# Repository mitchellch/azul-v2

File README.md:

# Azul Sprinkler System

## Main Purpose
The Azul Sprinkler System is a comprehensive, open-source irrigation control ecosystem designed for flexibility, resilience, and remote management. It is architected to support both standard wired irrigation zones and wireless, battery-operated "Zone Extenders" for areas without existing infrastructure. The entire system—from mobile app to firmware—is managed within this monorepo.

## Project Structure
This repository is a monorepo containing all components of the Azul system.

- **`mobile/`**: A cross-platform (iOS/Android) mobile application built with React Native and Expo. This is the primary user interface for controlling and monitoring the system.
- **`server/`**: The backend API and services. This component will handle business logic, data persistence, and communication between the apps and the hardware controllers. *(Not yet implemented)*
- **`firmware/`**: ESP32-based firmware for the physical sprinkler controllers. This includes code for the mains-powered Main Controller and the battery-powered Zone Extenders. *(Not yet implemented)*
- **`shared/`**: A directory for shared code, such as TypeScript types, constants, or validation schemas, that can be used across the mobile, server, and potentially firmware components.
- **`docs/`**: Contains all project documentation, including architecture diagrams, specifications, and bills of materials.

## Key Documentation
- **[Overall Architecture](docs/design/architecture.md):** A high-level overview of the entire system, its components, and how they interact.
- **[Zone Extender Specification](docs/design/zone-extender-spec.md):** Detailed technical specifications for the battery-powered, LoRa-based zone controller.
- **[Main Controller Bill of Materials](docs/hardware/main-controller-bom.md):** A complete list of electronic components for the main, wall-powered controller.

## Prerequisites

| Tool | Version | Notes |
|---|---|---|
| Node.js | 25.x | `node -v` to check |
| npm | 11.x | Ships with Node |
| Docker Desktop | 29.x+ | Runs PostgreSQL and Mosquitto |
| Android Studio | Panda 4+ | SDK, emulator, and `adb` |
| JDK 17 (Azul Zulu) | 17.x | At `/Library/Java/JavaVirtualMachines/zulu-17.jdk` |
| PlatformIO | Latest | VS Code extension or CLI — for firmware only |

Required shell config (`~/.zshrc`):

```bash
export JAVA_HOME=/Library/Java/JavaVirtualMachines/zulu-17.jdk/Contents/Home
export PATH=$JAVA_HOME/bin:$PATH
export ANDROID_HOME=$HOME/Library/Android/sdk
export PATH=$PATH:$ANDROID_HOME/platform-tools
```

> **macOS managed machine note:** A Salesforce Java stub at `/usr/local/bin/java` intercepts the `java` command. The `$JAVA_HOME/bin` prepend to `PATH` overrides it. If `java -version` shows a Salesforce warning instead of the JDK version, run `source ~/.zshrc`.

## Development Setup

The dev environment runs across **five terminal tabs** plus an Android emulator. Tabs are numbered by position, not startup order. Start services in this order: **Tab 5 (Docker) → Tab 4 (Server) → Tabs 2 & 3 (Mobile & Web, either order)**.

| Tab | Name | Description |
|-----|------|-------------|
| 1 | **Claude Code** | AI development agent (Anthropic CLI). Primary interaction point for editing code, running commands, and managing git. |
| 2 | **Mobile (Expo/React Native)** | Android app via `npx expo run:android`. BLE + cloud zone control, schedules, Auth0 native auth. |
| 3 | **Web (Next.js Dashboard)** | Next.js 14 browser dashboard on port 3001. Auth0 server-side sessions, REST proxy to backend, SSE zone updates, Tailwind CSS. |
| 4 | **Server (Express.js API)** | Node.js/TypeScript backend on port 3000. REST API, Auth0 JWT auth, Prisma ORM, MQTT client, SSE streams. |
| 5 | **Docker (Postgres + Mosquitto)** | Infrastructure services via Docker Compose. PostgreSQL 16 database and Eclipse Mosquitto 2 MQTT broker. Must start first. |
| — | **Firmware (VS Code + PlatformIO)** | Not a terminal tab. ESP32-S3 firmware built/flashed/monitored from VS Code with the PlatformIO extension. |

### 0. Connect an Android device

`npx expo run:android` needs a target device — either a physical phone or the emulator.

- **Physical phone (current setup):** Connect via USB with Developer Options and USB Debugging enabled. Run `adb devices` to confirm it appears.
- **Emulator (optional):** Open Android Studio → Device Manager → ▶ play on Pixel 9 (API 35). Wait for the home screen before proceeding.

### Tab 1 — Claude Code

```bash
cd ~/personal/dev/azul
claude
```

| | Details |
|---|---|
| **Tool** | Claude Code (Anthropic CLI) |
| **What it does** | AI-assisted development agent running in the terminal. Has full access to the repo for editing code, running commands, searching files, and managing git. This is the primary tab you interact with during development. |

### Tab 2 — Mobile app

```bash
cd mobile
npx expo run:android
```

| | Details |
|---|---|
| **Framework** | React Native 0.81 + Expo SDK 54 (TypeScript) |
| **Build tool** | Expo CLI — compiles native Android binary with linked native modules, then starts Metro bundler |
| **What it does** | Primary user interface. Auth via `react-native-auth0`, BLE communication via `react-native-ble-plx`, cloud communication via REST polling to the backend API. Manages zone control (start/stop/queue), schedules, and controller settings. |
| **Key env vars** | `EXPO_PUBLIC_API_URL`, `EXPO_PUBLIC_AUTH0_DOMAIN`, `EXPO_PUBLIC_AUTH0_CLIENT_ID` (in `mobile/.env` and `mobile/.env.local`) |

> **Important:** This project uses native modules (BLE, Auth0) that require a development build. **Do NOT use `npx expo start`** — that launches Expo Go, which cannot load native modules. Always use `npx expo run:android`.

> **Env var changes:** `EXPO_PUBLIC_*` vars are baked in at Metro startup. After editing `.env` or `.env.local`, restart Metro with `npx expo start --reset-cache`, then press `a` to relaunch on Android.

First build takes 2–3 minutes (compiles native code). Subsequent runs are faster (~30s). The app installs and launches on the emulator automatically.

### Tab 3 — Web dashboard

```bash
cd web
npm run dev
```

| | Details |
|---|---|
| **Framework** | Next.js 14 (TypeScript, App Router) |
| **Port** | `localhost:3001` |
| **What it does** | Browser-based dashboard for controlling irrigation. Auth via `@auth0/nextjs-auth0` (server-side sessions). Proxies API requests to the backend at `localhost:3000`. Receives real-time zone updates via SSE (Server-Sent Events) through a fetch-based stream. Styled with Tailwind CSS. |
| **Key env vars** | `AUTH0_SECRET`, `AUTH0_BASE_URL`, `AUTH0_ISSUER_BASE_URL`, `AUTH0_CLIENT_ID`, `AUTH0_CLIENT_SECRET`, `AUTH0_AUDIENCE`, `NEXT_PUBLIC_API_URL` (in `web/.env.local`) |

Open `http://localhost:3001` in a browser. You'll be redirected to Auth0 for login (Google OAuth).

### Tab 4 — Backend API server

```bash
cd server
npm run dev
```

| | Details |
|---|---|
| **Framework** | Express.js (Node.js / TypeScript) |
| **Runner** | `tsx watch` — auto-reloads on file changes |
| **Port** | `localhost:3000` |
| **What it does** | REST API for devices, zones, schedules, and users. Authenticates requests via Auth0 JWTs. Connects to PostgreSQL via Prisma ORM and to Mosquitto via MQTT.js. Maintains an in-memory zone state cache from MQTT status messages. Serves SSE streams to the web app. Runs an offline-sweep job to detect disconnected controllers. |
| **Key env vars** | `DATABASE_URL`, `MQTT_URL`, `AUTH0_DOMAIN`, `AUTH0_AUDIENCE` (in `server/.env`) |

You should see `Server listening on port 3000` and `[MQTT] Connected to mqtt://localhost:1883`.

### Tab 5 — Docker infrastructure

```bash
cd server
docker compose up
```

| What it runs | Details |
|---|---|
| **PostgreSQL 16** (Alpine) | Relational database. Stores users, devices, zones, schedules, audit logs. Accessible at `localhost:5432`, credentials `azul/azul/azul` (user/password/database). Data persists in a Docker volume (`postgres_data`). |
| **Eclipse Mosquitto 2** | MQTT message broker. Relays commands and status between the backend server and ESP32 controllers. Listens on `localhost:1883` (MQTT) and `localhost:9001` (WebSocket). Anonymous access enabled for local dev. |

Leave this tab running. You should see `database system is ready to accept connections` and `mosquitto version 2.x.x running`.

### Firmware (VS Code + PlatformIO)

Firmware development uses **VS Code with the PlatformIO extension** — not a terminal tab. Open the `firmware/main-controller` folder in VS Code as a PlatformIO project.

| Action | How |
|---|---|
| **Build** | PlatformIO sidebar → Build, or `pio run -e esp32-s3` |
| **Flash** | Connect ESP32 via USB → PlatformIO sidebar → Upload, or `pio run --target upload -e esp32-s3` |
| **Serial monitor** | PlatformIO sidebar → Monitor, or `pio device monitor --baud 115200` |
| **Build + Flash + Monitor** | PlatformIO sidebar → Upload and Monitor |

| | Details |
|---|---|
| **Platform** | ESP32-S3 (N16R8), Arduino framework |
| **Build system** | PlatformIO |
| **What it does** | Runs on the physical irrigation controller. Manages zone GPIOs (solenoid drivers), WiFi connectivity, MQTT communication with the backend, BLE GATT server for mobile app pairing, NTP time sync, schedule execution, and a serial CLI for debugging. |
| **Integration tests** | `python3 -m pytest tests/integration/ --host=<controller-ip> -q` (requires controller on same network) |

### Service dependency graph

```
Docker (Postgres + Mosquitto)
  └── Backend API server (connects to both)
        ├── Mobile app (REST polling to backend)
        ├── Web app (REST proxy + SSE from backend)
        └── ESP32 firmware (MQTT via Mosquitto)
```

### First-time setup

If this is a fresh clone or the Docker volume was wiped:

```bash
cd server
npm install
npx prisma db push       # creates tables in PostgreSQL
npx prisma generate       # generates the Prisma client

cd ../mobile
npm install

cd ../web
npm install
```

### Stopping everything

1. **Ctrl+C** in each terminal tab (mobile, server, web, Docker)
2. Close the Android emulator from Android Studio Device Manager
3. Docker volumes persist — your database data survives restarts

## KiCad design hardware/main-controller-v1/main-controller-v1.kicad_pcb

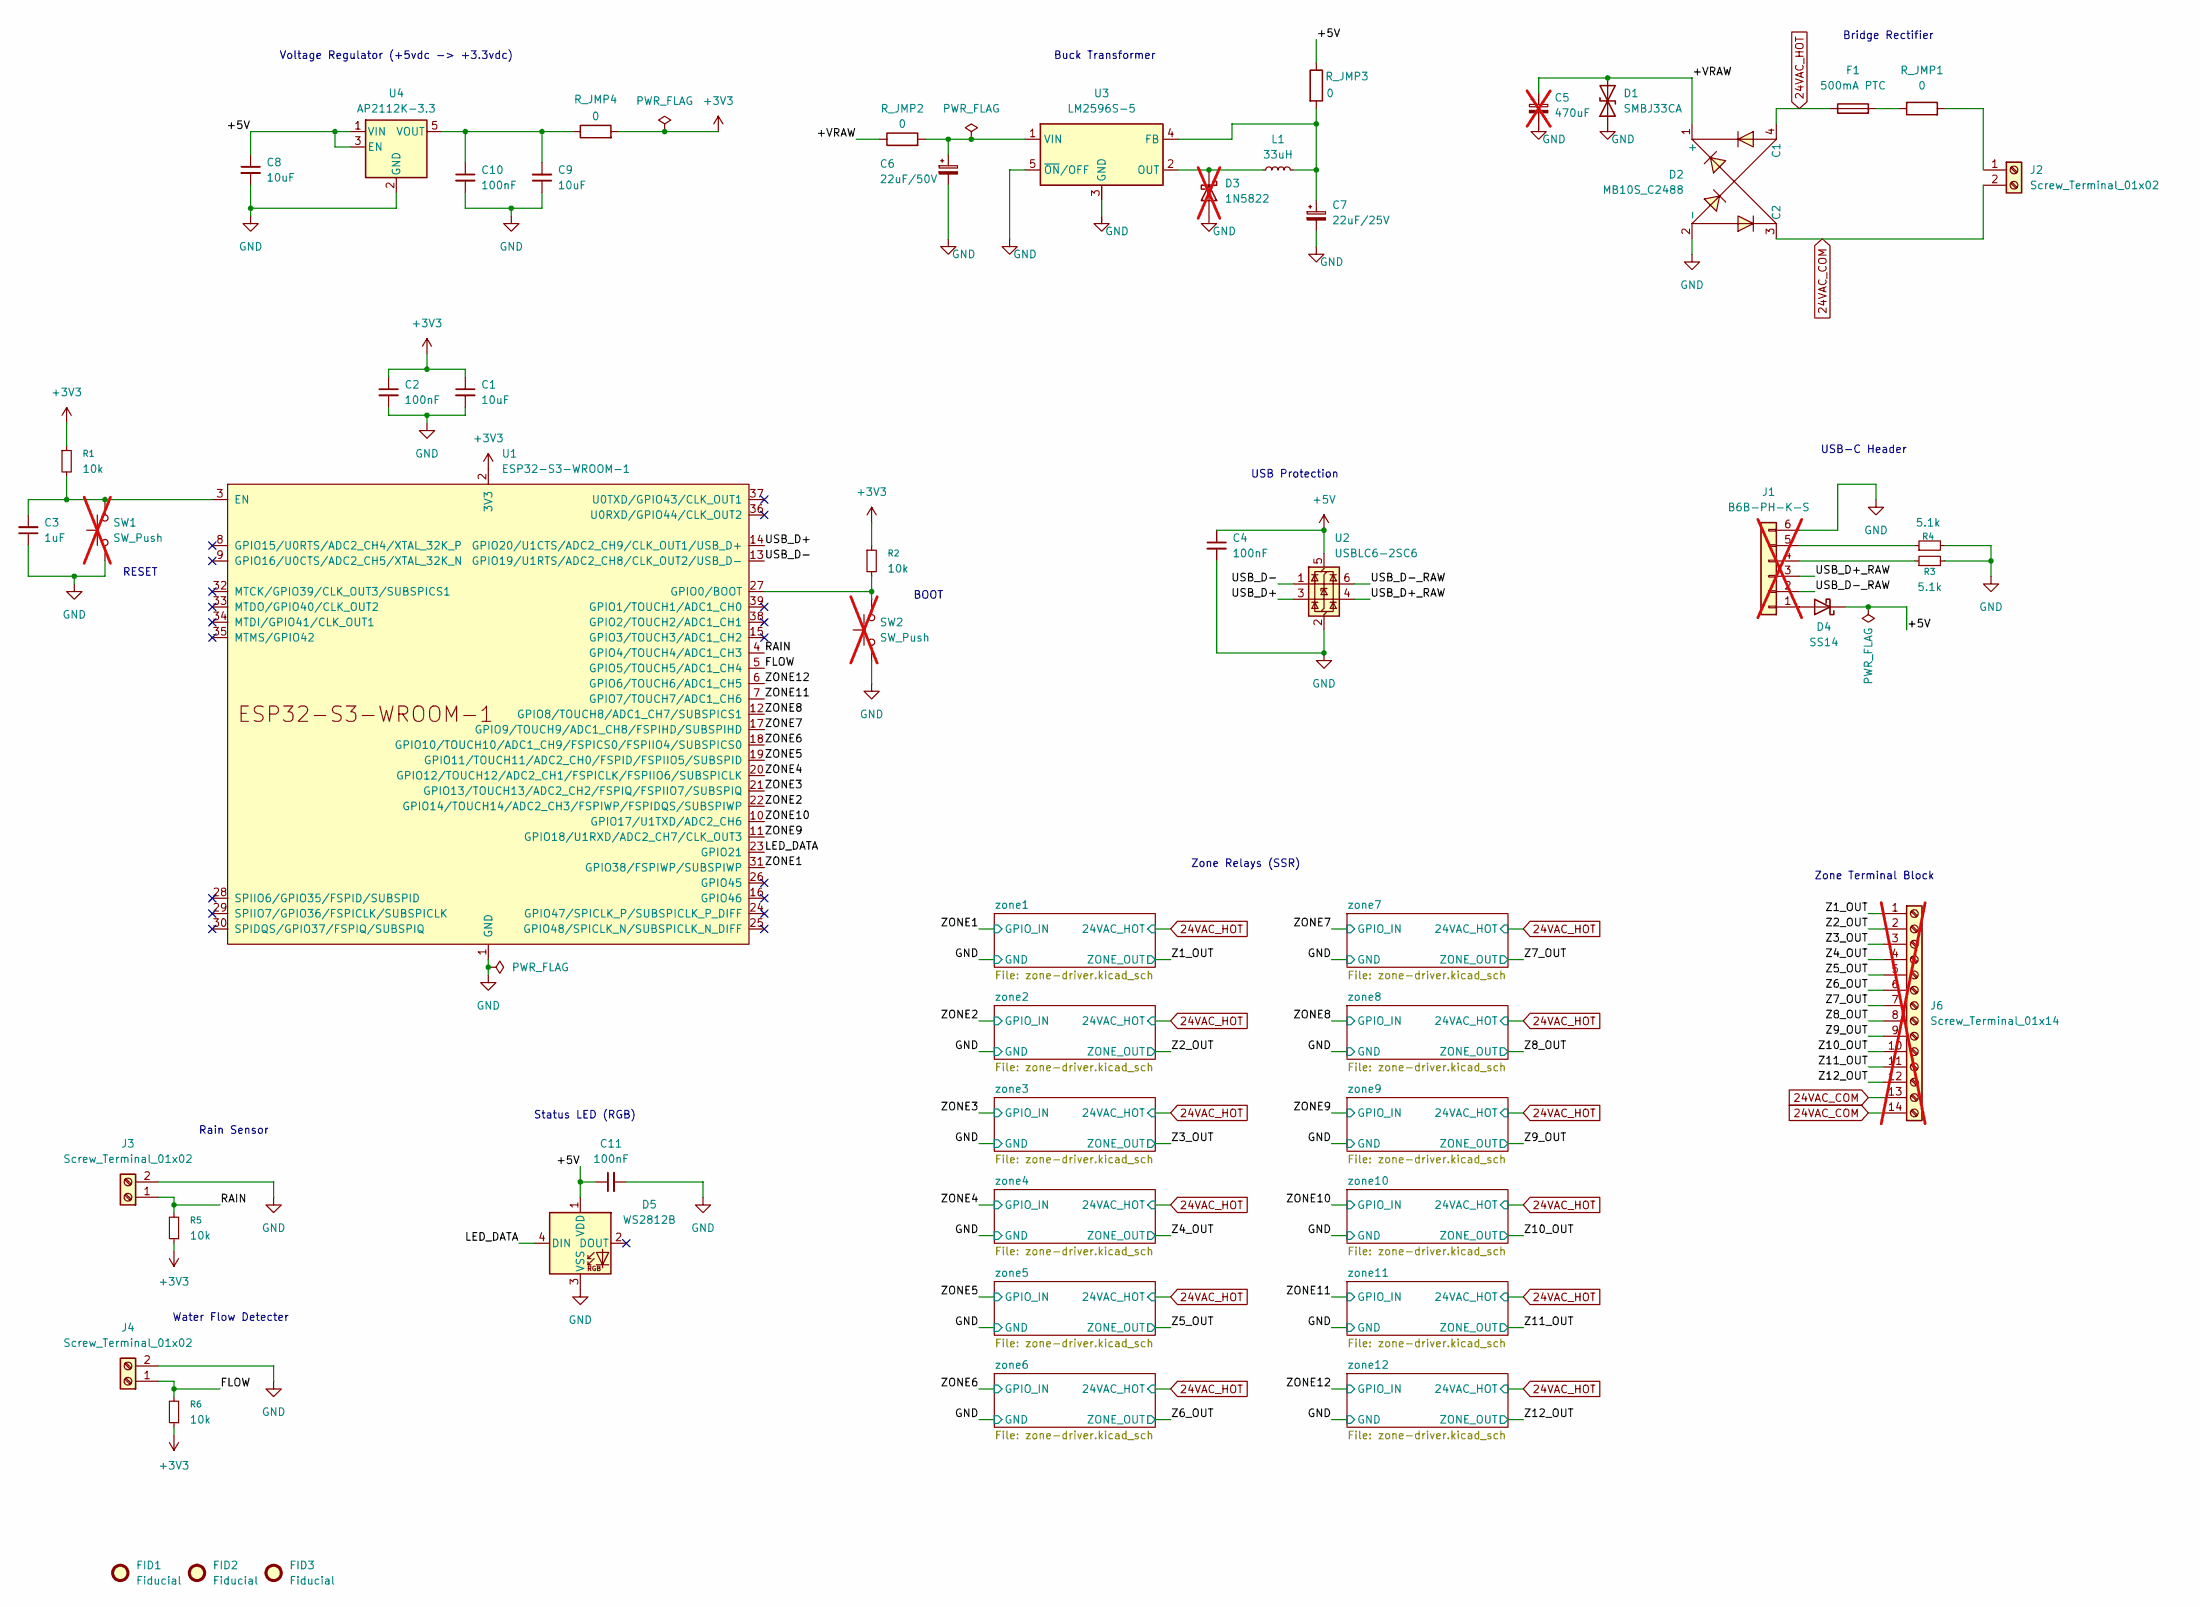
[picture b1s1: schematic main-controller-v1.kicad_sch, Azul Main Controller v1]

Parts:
C1, C8, C9: 10uF; C_0805_2012Metric; LCSC C15850
C2, C4, C10, C11: 100nF; C_0603_1608Metric; LCSC C14663
C3: 1uF; C_0603_1608Metric; LCSC C15849
C5: 470uF; CP_Radial_D10.0mm_P5.00mm; not fitted
C6: 22uF/50V; CP_Elec_6.3x5.4; LCSC C2836438
C7: 22uF/25V; CP_Elec_5x5.8; LCSC C178541
D1: SMBJ33CA; D_SMB; LCSC C78420
D2: MB10S_C2488; MBS_L4.7-W3.8-P2.40-LS7.0-TL; MPN MB10S-50MIL; LCSC C2488
D3: 1N5822; D_DO-201AD_P15.24mm_Horizontal; not fitted
D4: SS14; D_SMA; LCSC C2480
D5: WS2812B; LED_WS2812B_PLCC4_5.0x5.0mm_P3.2mm; LCSC C2761795
F1: 500mA PTC; Fuse_1812_4532Metric; LCSC C17313
FID1, FID2, FID3: Fiducial; Fiducial_1mm_Mask2mm
J1: B6B-PH-K-S; JST_PH_B6B-PH-K_1x06_P2.00mm_Vertical; LCSC C131357; not fitted
J2, J3, J4: Screw_Terminal_01x02; TerminalBlock_MaiXu_MX126-5.0-02P_1x02_P5.00mm; LCSC C5188434
J6: Screw_Terminal_01x14; TerminalBlock_MaiXu_MX126-5.0-14P_1x14_P5.00mm; not fitted
L1: 33uH; L_Bourns_SRR1260; LCSC C840528
R1, R2, R5, R6: 10k; R_0603_1608Metric; LCSC C25804
R3, R4: 5.1k; R_0603_1608Metric; LCSC C23186
R_JMP1, R_JMP2, R_JMP3, R_JMP4: 0; R_1206_3216Metric; LCSC C17168
SW1, SW2: SW_Push; SW_PUSH_6mm; not fitted
U1: ESP32-S3-WROOM-1; LCSC C2913204
U2: USBLC6-2SC6; SOT-23-6; LCSC C7519
U3: LM2596S-5; TO-263-5_TabPin3; LCSC C5276750
U4: AP2112K-3.3; SOT-23-5; LCSC C51118

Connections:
24VAC_COM: D2.3 (C2), J2.2, J6.13, J6.14
24VAC_HOT: D2.4 (C1), F1.1; also elsewhere on the board
+3V3: C1.1, C2.1, R1.1, R2.1, R5.1, R6.1, R_JMP4.2, U1.2 (3V3)
+5V: C4.1, C8.1, C11.1, D4.1 (K), D5.1 (VDD), R_JMP3.1, U2.5 (VBUS), U4.1 (VIN), U4.3 (EN)
/+VRAW: C5.1, D1.2 (A2), D2.1 (+), R_JMP2.1
/FLOW: J4.1, R6.2, U1.5 (GPIO5/TOUCH5/ADC1_CH4)
/LED_DATA: D5.4 (DIN), U1.23 (GPIO21)
/RAIN: J3.1, R5.2, U1.4 (GPIO4/TOUCH4/ADC1_CH3)
/USB_D+: U1.14 (GPIO20/U1CTS/ADC2_CH9/CLK_OUT1/USB_D+), U2.3 (I/O2)
/USB_D+_RAW: J1.3, U2.4 (I/O2)
/USB_D-: U1.13 (GPIO19/U1RTS/ADC2_CH8/CLK_OUT2/USB_D-), U2.1 (I/O1)
/USB_D-_RAW: J1.2, U2.6 (I/O1)
/Z1_OUT: J6.1; also elsewhere on the board
/Z2_OUT: J6.2; also elsewhere on the board
/Z3_OUT: J6.3; also elsewhere on the board
/Z4_OUT: J6.4; also elsewhere on the board
/Z5_OUT: J6.5; also elsewhere on the board
/Z6_OUT: J6.6; also elsewhere on the board
/Z7_OUT: J6.7; also elsewhere on the board
/Z8_OUT: J6.8; also elsewhere on the board
/Z9_OUT: J6.9; also elsewhere on the board
/Z10_OUT: J6.10; also elsewhere on the board
/Z11_OUT: J6.11; also elsewhere on the board
/Z12_OUT: J6.12; also elsewhere on the board
/ZONE1: U1.31 (GPIO38/FSPIWP/SUBSPIWP); also elsewhere on the board
/ZONE2: U1.22 (GPIO14/TOUCH14/ADC2_CH3/FSPIWP/FSPIDQS/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); also elsewhere on the board
/ZONE3: U1.21 (GPIO13/TOUCH13/ADC2_CH2/FSPIQ/FSPIIO7/S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); also elsewhere on the board
/ZONE4: U1.20 (GPIO12/TOUCH12/ADC2_CH1/FSPICLK/FSPIIO6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); also elsewhere on the board
/ZONE5: U1.19 (GPIO11/TOUCH11/ADC2_CH0/FSPID/FSPIIO5/S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); also elsewhere on the board
/ZONE6: U1.18 (GPIO10/TOUCH10/ADC1_CH9/FSPICS0/FSPIIO4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); also elsewhere on the board
/ZONE7: U1.17 (GPIO9/TOUCH9/ADC1_CH8/FSPIHD/SUBSPIHD); also elsewhere on the board
/ZONE8: U1.12 (GPIO8/TOUCH8/ADC1_CH7/SUBSPICS1); also elsewhere on the board
/ZONE9: U1.11 (GPIO18/U1RXD/ADC2_CH7/CLK_OUT3); also elsewhere on the board
/ZONE10: U1.10 (GPIO17/U1TXD/ADC2_CH6); also elsewhere on the board
/ZONE11: U1.7 (GPIO7/TOUCH7/ADC1_CH6); also elsewhere on the board
/ZONE12: U1.6 (GPIO6/TOUCH6/ADC1_CH5); also elsewhere on the board
GND: C1.2, C2.2, C3.1, C4.2, C5.2, C6.2, C7.2, C8.2, C9.1, C10.2, C11.2, D1.1 (A1), D2.2 (-), D3.2 (A), D5.3 (VSS), J1.6, J3.2, J4.2, R3.2, R4.2, SW1.1, SW2.1, U1.1 (GND), U1.40 (GND), U1.41 (GND), U2.2 (GND), U3.3 (GND), U3.5 (~ON/OFF), U4.2 (GND); also elsewhere on the board
unnamed: D3.1 (K), L1.1, U3.2 (OUT)
unnamed: D4.2 (A), J1.1
unnamed: F1.2, R_JMP1.1
unnamed: J1.4, R3.1
unnamed: J1.5, R4.1
unnamed: J2.1, R_JMP1.2
unnamed: C3.2, R1.2, SW1.2, U1.3 (EN)
unnamed: R2.2, SW2.2, U1.27 (GPIO0/BOOT)
unnamed: C7.1, L1.2, R_JMP3.2, U3.4 (FB)
unnamed: C6.1, R_JMP2.2, U3.1 (VIN)
unnamed: C9.2, C10.1, R_JMP4.1, U4.5 (VOUT)

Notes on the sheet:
Zone Terminal Block
BOOT
Buck Transformer
Voltage Regulator (+5vdc -> +3.3vdc)
USB Protection
USB-C Header
Zone Relays (SSR)
Status LED (RGB)
Rain Sensor
RESET
Water Flow Detecter
Bridge Rectifier

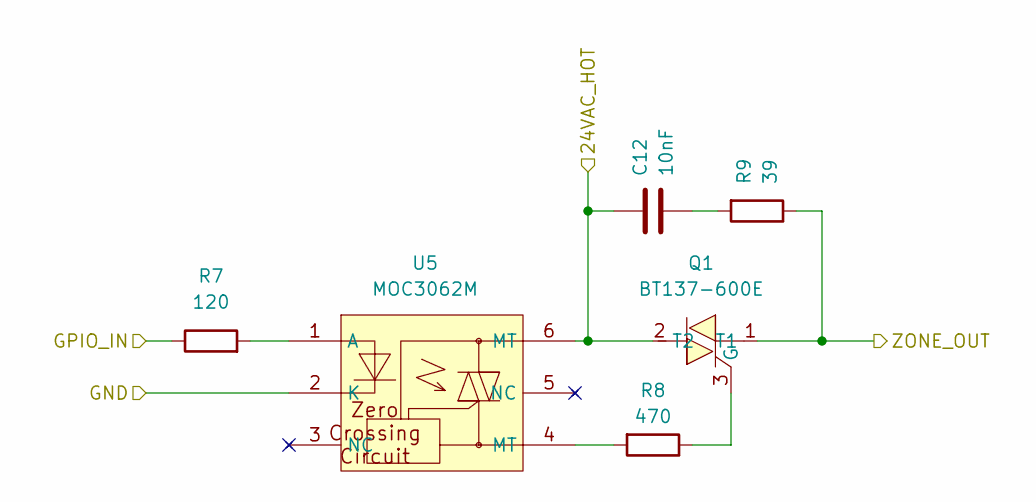
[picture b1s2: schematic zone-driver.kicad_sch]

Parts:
C12: 10nF; CAP-TH_L13.0-W5.0-P10.00-D1.0; LCSC C105755
Q1: BT137-600E; TO-220-3_L10.0-W4.5-P2.54-L; MPN BT137-600E; LCSC C967624
R7: 120; R_0805_2012Metric; LCSC C17437
R8: 470; R_0805_2012Metric; LCSC C17710
R9: 39; R_2010_5025Metric; LCSC C2692665
U5: MOC3062M; DIP-6_L8.5-W6.4-P2.54-LS7.6-BL; MPN MOC3062M; LCSC C8919

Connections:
24VAC_HOT: C12.1, Q1.2 (T2), U5.6 (MT); also elsewhere on the board
/Z1_OUT: Q1.1 (T1), R9.1; also elsewhere on the board
/ZONE1: R7.1; also elsewhere on the board
GND: U5.2 (K); also elsewhere on the board
unnamed: C12.2, R9.2
unnamed: Q1.3 (G), R8.1
unnamed: R8.2, U5.4 (MT)
unnamed: R7.2, U5.1 (A)

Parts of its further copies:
C13, C14, C15, C16, C17, C18, C19, C20, C21, C22, C23: 10nF; CAP-TH_L13.0-W5.0-P10.00-D1.0; LCSC C105755
Q2, Q3, Q4, Q5, Q6, Q7, Q8, Q9, Q10, Q11, Q12: BT137-600E; TO-220-3_L10.0-W4.5-P2.54-L; MPN BT137-600E; LCSC C967624
R10, R13, R16, R19, R22, R25, R28, R31, R34, R37, R40: 120; R_0805_2012Metric; LCSC C17437
R11, R14, R17, R20, R23, R26, R29, R32, R35, R38, R41: 470; R_0805_2012Metric; LCSC C17710
R12, R15, R18, R21, R24, R27, R30, R33, R36, R39, R42: 39; R_2010_5025Metric; LCSC C2692665
U6, U7, U8, U9, U10, U11, U12, U13, U14, U15, U16: MOC3062M; DIP-6_L8.5-W6.4-P2.54-LS7.6-BL; MPN MOC3062M; LCSC C8919

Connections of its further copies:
24VAC_HOT: C13.1, C14.1, C15.1, C16.1, C17.1, C18.1, C19.1, C20.1, C21.1, C22.1, C23.1, Q2.2 (T2), Q3.2 (T2), Q4.2 (T2), Q5.2 (T2), Q6.2 (T2), Q7.2 (T2), Q8.2 (T2), Q9.2 (T2), Q10.2 (T2), Q11.2 (T2), Q12.2 (T2), U6.6 (MT), U7.6 (MT), U8.6 (MT), U9.6 (MT), U10.6 (MT), U11.6 (MT), U12.6 (MT), U13.6 (MT), U14.6 (MT), U15.6 (MT), U16.6 (MT); also elsewhere on the board
/Z2_OUT: Q2.1 (T1), R12.1; also elsewhere on the board
/Z3_OUT: Q3.1 (T1), R15.1; also elsewhere on the board
/Z4_OUT: Q4.1 (T1), R18.1; also elsewhere on the board
/Z5_OUT: Q5.1 (T1), R21.1; also elsewhere on the board
/Z6_OUT: Q6.1 (T1), R24.1; also elsewhere on the board
/Z7_OUT: Q7.1 (T1), R27.1; also elsewhere on the board
/Z8_OUT: Q8.1 (T1), R30.1; also elsewhere on the board
/Z9_OUT: Q9.1 (T1), R33.1; also elsewhere on the board
/Z10_OUT: Q10.1 (T1), R36.1; also elsewhere on the board
/Z11_OUT: Q11.1 (T1), R39.1; also elsewhere on the board
/Z12_OUT: Q12.1 (T1), R42.1; also elsewhere on the board
/ZONE2: R10.1; also elsewhere on the board
/ZONE3: R13.1; also elsewhere on the board
/ZONE4: R16.1; also elsewhere on the board
/ZONE5: R19.1; also elsewhere on the board
/ZONE6: R22.1; also elsewhere on the board
/ZONE7: R25.1; also elsewhere on the board
/ZONE8: R28.1; also elsewhere on the board
/ZONE9: R31.1; also elsewhere on the board
/ZONE10: R34.1; also elsewhere on the board
/ZONE11: R37.1; also elsewhere on the board
/ZONE12: R40.1; also elsewhere on the board
GND: U6.2 (K), U7.2 (K), U8.2 (K), U9.2 (K), U10.2 (K), U11.2 (K), U12.2 (K), U13.2 (K), U14.2 (K), U15.2 (K), U16.2 (K); also elsewhere on the board
unnamed: C13.2, R12.2
unnamed: C14.2, R15.2
unnamed: C15.2, R18.2
unnamed: C16.2, R21.2
unnamed: C17.2, R24.2
unnamed: C18.2, R27.2
unnamed: C19.2, R30.2
unnamed: C20.2, R33.2
unnamed: C21.2, R36.2
unnamed: C22.2, R39.2
unnamed: C23.2, R42.2
unnamed: Q2.3 (G), R11.1
unnamed: Q3.3 (G), R14.1
unnamed: Q4.3 (G), R17.1
unnamed: Q5.3 (G), R20.1
unnamed: Q6.3 (G), R23.1
unnamed: Q7.3 (G), R26.1
unnamed: Q8.3 (G), R29.1
unnamed: Q9.3 (G), R32.1
unnamed: Q10.3 (G), R35.1
unnamed: Q11.3 (G), R38.1
unnamed: Q12.3 (G), R41.1
unnamed: R11.2, U6.4 (MT)
unnamed: R14.2, U7.4 (MT)
unnamed: R17.2, U8.4 (MT)
unnamed: R20.2, U9.4 (MT)
unnamed: R23.2, U10.4 (MT)
unnamed: R26.2, U11.4 (MT)
unnamed: R29.2, U12.4 (MT)
unnamed: R32.2, U13.4 (MT)
unnamed: R35.2, U14.4 (MT)
unnamed: R38.2, U15.4 (MT)
unnamed: R41.2, U16.4 (MT)
unnamed: R10.2, U6.1 (A)
unnamed: R13.2, U7.1 (A)
unnamed: R16.2, U8.1 (A)
unnamed: R19.2, U9.1 (A)
unnamed: R22.2, U10.1 (A)
unnamed: R25.2, U11.1 (A)
unnamed: R28.2, U12.1 (A)
unnamed: R31.2, U13.1 (A)
unnamed: R34.2, U14.1 (A)
unnamed: R37.2, U15.1 (A)
unnamed: R40.2, U16.1 (A)

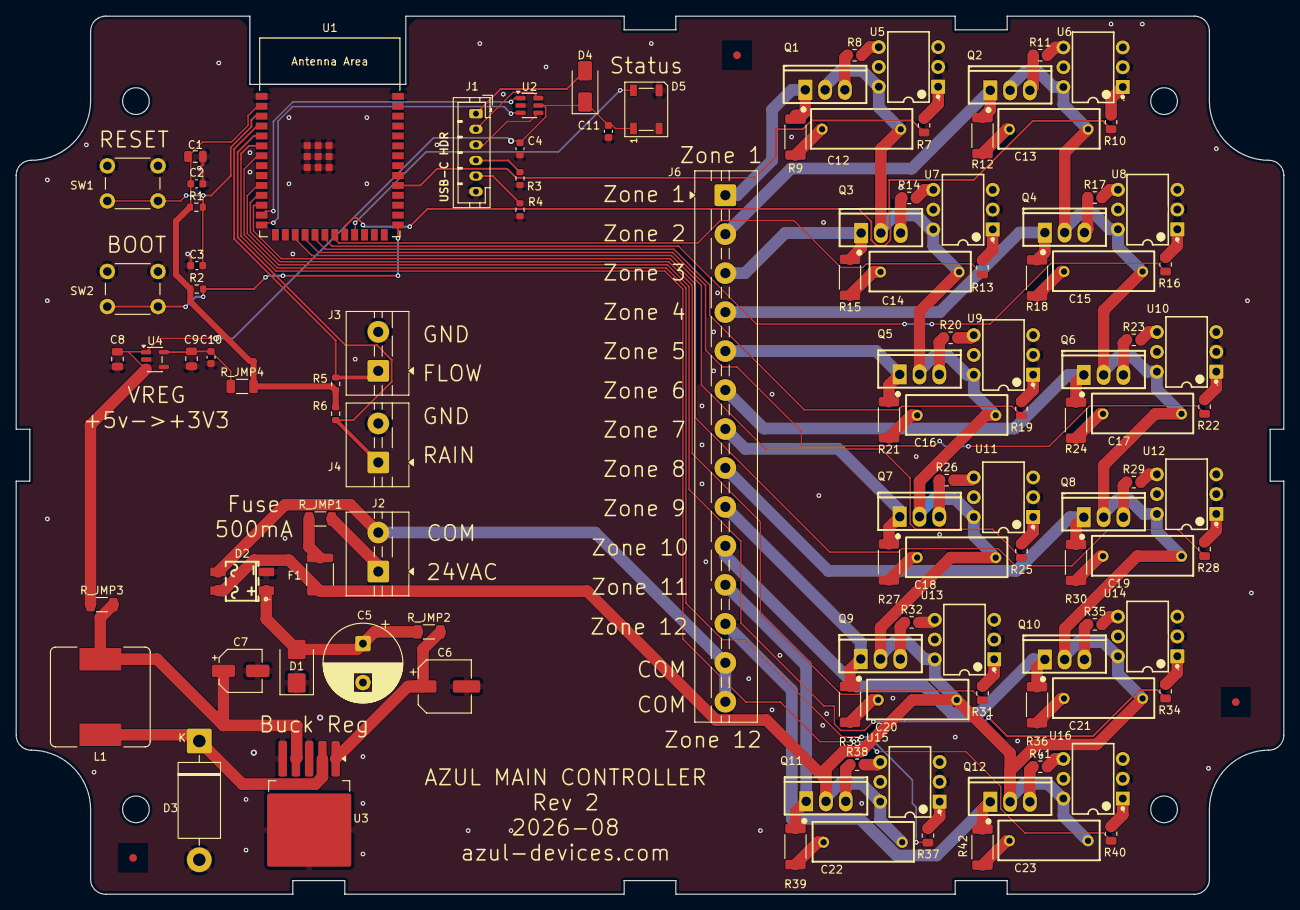
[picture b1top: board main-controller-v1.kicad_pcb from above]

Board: 2 copper layers, 162.7 x 112.7 mm, 114 parts (0 on the bottom side), 96 nets.

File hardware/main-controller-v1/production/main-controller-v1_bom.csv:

"Designator","Footprint","Quantity","Value","LCSC Part #"
"C1,C8,C9","Capacitor_SMD:C_0805_2012Metric","3","10uF","C15850"
"C2,C4,C10,C11","Capacitor_SMD:C_0603_1608Metric","4","100nF","C14663"
"C3","Capacitor_SMD:C_0603_1608Metric","1","1uF","C15849"
"C6","Capacitor_SMD:CP_Elec_6.3x5.4","1","22uF/50V","C2836438"
"C7","Capacitor_SMD:CP_Elec_5x5.8","1","22uF/25V","C178541"
"C12,C13,C14,C15,C16,C17,C18,C19,C20,C21,C22,C23","Azul:CAP-TH_L13.0-W5.0-P10.00-D1.0","12","10nF","C105755"
"D1","Diode_SMD:D_SMB","1","SMBJ33CA","C78420"
"D2","Azul:MBS_L4.7-W3.8-P2.40-LS7.0-TL","1","MB10S_C2488","C2488"
"D4","Diode_SMD:D_SMA","1","SS14","C2480"
"D5","LED_SMD:LED_WS2812B_PLCC4_5.0x5.0mm_P3.2mm","1","WS2812B","C2761795"
"F1","Fuse:Fuse_1812_4532Metric","1","500mA PTC","C17313"
"J2,J3,J4","TerminalBlock:TerminalBlock_MaiXu_MX126-5.0-02P_1x02_P5.00mm","3","Screw_Terminal_01x02","C5188434"
"L1","Inductor_SMD:L_Bourns_SRR1260","1","33uH","C840528"
"Q1,Q2,Q3,Q4,Q5,Q6,Q7,Q8,Q9,Q10,Q11,Q12","Azul:TO-220-3_L10.0-W4.5-P2.54-L","12","BT137-600E","C967624"
"R1,R2,R5,R6","Resistor_SMD:R_0603_1608Metric","4","10k","C25804"
"R3,R4","Resistor_SMD:R_0603_1608Metric","2","5.1k","C23186"
"R7,R10,R13,R16,R19,R22,R25,R28,R31,R34,R37,R40","Resistor_SMD:R_0805_2012Metric","12","120","C17437"
"R8,R11,R14,R17,R20,R23,R26,R29,R32,R35,R38,R41","Resistor_SMD:R_0805_2012Metric","12","470","C17710"
"R9,R12,R15,R18,R21,R24,R27,R30,R33,R36,R39,R42","Resistor_SMD:R_2010_5025Metric","12","39","C2692665"
"R_JMP1,R_JMP2,R_JMP3,R_JMP4","Resistor_SMD:R_1206_3216Metric","4","0","C17168"
"U1","PCM_Espressif:ESP32-S3-WROOM-1","1","ESP32-S3-WROOM-1","C2913204"
"U2","Package_TO_SOT_SMD:SOT-23-6","1","USBLC6-2SC6","C7519"
"U3","Package_TO_SOT_SMD:TO-263-5_TabPin3","1","LM2596S-5","C5276750"
"U4","Package_TO_SOT_SMD:SOT-23-5","1","AP2112K-3.3","C51118"
"U5,U6,U7,U8,U9,U10,U11,U12,U13,U14,U15,U16","Azul:DIP-6_L8.5-W6.4-P2.54-LS7.6-BL","12","MOC3062M","C8919"

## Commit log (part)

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2026-04-25 Initial commit
    Generated by create-expo-app 3.5.3.
2026-05-02 feat: Initial monorepo setup and project restructuring\n\n- Restructured project into a monorepo with dedicated directories for mobile, server, firmware, shared, and docs.\n- Migrated existing Expo m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
2026-05-07 chore: reorganize repo structure and documentation
    - Rename all docs to kebab-case and move to subdirectories (design/, hardware/, requirements/, business/)
    - Move Extender_v2_Spec and Provisioning_Flow into docs/design/
    - Add docs/README.md as a full documentation index
    - Add CLAUDE.md with project context and tech stack for Claude Code
    - Scaffold mobile/ internal directories (app/, components/, hooks/, services/, store/)
    - Scaffold firmware/ PlatformIO layout (main-controller/, zone-extender/, lib/)
2026-05-07 feat(firmware): add main-controller v0.1.0 skeleton
    - ZoneController: 8-zone state machine with start/stop/auto-expiry timers
    - WiFiManager: connect on boot, auto-reconnect every 30s, NVS credential storage
    - RestServer: HTTP REST API on port 80 — full zone CRUD + status endpoint
    - BleServer: NimBLE GATT server with status notify, zone command write, zone data read
    - CLI: USB serial REPL — zone control, WiFi setup, version, reboot commands
    - Versioning: SemVer in version.h + git SHA/dirty flag injected at build time via PlatformIO pre-build script
2026-05-07 test(firmware): add ZoneController unit tests — 21/21 passing
    - Native PlatformIO test environment (runs on host, no device needed)
    - Arduino stub header for host-side compilation
    - 21 tests covering: init state, startZone, stopZone, stopAll, setZoneName, getZone, tick expiry
    - Run with: pio test -e native
2026-05-07 fix(firmware): fix REST route ordering and NVS first-boot error
    - Reorder routes so specific regex paths match before generic /api/zones
    (GET /api/zones/1 was returning all zones instead of a single zone)
    - Open NVS namespace in read/write mode so it's created on first boot
    (was logging nvs_open failed: NOT_FOUND on blank devices)
    - Add upload_protocol = esp-builtin for reliable flashing on ESP32-S3 DevKit
    Verified on hardware: all REST endpoints working correctly.
2026-05-07 docs(firmware): document integration test command and structure
2026-05-07 feat(firmware): temperature F, SSID in status, build timestamp, CLI/logger fixes
    - Add temperature_f to REST, BLE, and CLI status output
    - Add SSID to REST status response
    - Add build timestamp (FW_BUILD_DATE/TIME) to version command and REST status
    - Fix Logger: boot-time messages use Serial directly (no prompt padding during boot)
    - Fix CLI: empty Enter now prints a new prompt instead of doing nothing
    - Fix WiFi: require 2 consecutive failed checks before reconnecting (avoids blips)
2026-05-07 feat(firmware): add scheduling system
    New modules:
    - ScheduleModel.h: Schedule, ScheduleRun, AuditEntry, ChangeEntry structs
    - TimeManager: NTP sync, timezone storage, ISO date ↔ days-since-epoch conversion
    - ScheduleStore: NVS ring buffer (5 slots) for schedule CRUD + active UUID
    - AuditLog: NVS ring buffer (256 entries) for zone activation events, batch-flushed
    - ChangeLog: NVS ring buffer (32 entries) for schedule CRUD history
2026-05-08 fix(firmware): fix schedule PUT routing and scheduler state bugs — 79/79 tests passing
    REST routing:
    - PUT /api/schedules/:id was being intercepted by AsyncCallbackJsonWebHandler for POST
    - Fixed by routing both POST and PUT through same handler with URL/method guard
    - DELETE /api/schedules/nonexistent now correctly returns 404 (not 409)
    - /api/log/changes routing fixed — was matching /api/log prefix
    Scheduler bugs:
2026-05-08 feat(firmware): timezone management — CLI commands, REST API, consistent date/time display
    CLI:
    - tz-get: show current offset, name, and source (manual/not set)
    - tz-set <+/-HH:MM>: set timezone offset manually, persists to NVS
    - status: renamed Time to Date/Time, removed timezone name (redundant with tz-get)
    - cmdStatus: added TimeManager& reference for direct access
    REST:
2026-05-08 docs: expand cloud architecture with Terraform strategy, MQTT protocol, dev/prod stack
2026-05-08 feat(firmware): ZoneQueue, ZoneLed, unified zone scheduling
    ZoneQueue:
    - All zone starts (CLI, REST, BLE, Scheduler) route through a single queue
    - Sequencing enforced: one zone at a time, others wait
    - Queue depth: 16 entries
    - stop <id> cancels from queue or stops if running
    - stop-all clears queue and stops running zone
2026-05-08 docs(server): comprehensive local dev setup guide with Docker, MQTT, database management
2026-05-09 docs: web app architecture and updated cloud architecture with multi-tenant model
2026-05-09 feat(server): P5 SSE real-time status streaming
    - sseRegistry: in-process pub/sub for per-device live events
    - MQTT status handler emits to connected SSE clients on each heartbeat
    - GET /api/devices/:mac/stream — SSE endpoint with auth + ownership check
    - Sends immediate snapshot on connect, live status updates as they arrive
    - 30s heartbeat keeps connections alive through proxies
2026-05-09 docs(server): comprehensive API documentation and README
    - Full endpoint reference with request/response shapes
    - MQTT protocol table
    - Device claiming flow explanation
    - Database command reference
    - Testing instructions with M2M token example
    - Updated P7 dashboard status to complete
2026-05-10 feat(mobile): register controller with backend cloud API
    - cloudApi.ts: typed API client using Auth0 access token
    - Controller store: cloudId and mac fields
    - adopt.tsx: calls POST /api/devices/claim after BLE claim (best-effort)
    - settings.tsx: Cloud section shows registration status; Register button
    for already-adopted controllers when backend is available
    - EXPO_PUBLIC_API_URL env var for backend URL
2026-05-10 feat: end-to-end cloud connectivity — MQTT, web dashboard, fixed data issues
    Firmware:
    - mqtt-set / mqtt-status CLI commands to configure broker address
    - offlineSweep: catch DB errors silently (prevents crash when DB down)
    Backend:
    - requireUser: only update email/name when JWT actually provides them
    (prevents empty-string collision on unique email constraint)
2026-05-10 fix(web): zone status from MQTT, clean badge UI, better slider labels
    - Firmware: MQTT status now includes per-zone status array
    - Web SSE handler: parses zones array from MQTT status events
    - Badge: removed per-badge text hints, single instruction above grid
    - Status text transparent (not shown) when idle, removes clutter
    - Removed polling loop — SSE + optimistic updates only
    - Click running zone to stop (cursor changes to indicate it)
2026-05-10 feat(web): full schedule CRUD editor, fixed slider labels, tab order
    - ScheduleEditor component: name, start/end dates, zone schedules
    with zone picker, time inputs, duration chips, day-of-week or
    every-N-days repeat mode
    - Schedules tab: list with Edit/Delete/Activate, + New Schedule button
    - Tab order matches mobile: Schedules / Zones / Logs
    - Default tab is Schedules
2026-05-10 feat(web): accessible month/day selects for any-year schedule dates
    Replace text inputs with native <select> elements for month and day
    when 'Repeat every year' is checked. Native selects are fully keyboard
    navigable, screen reader compatible, and mobile-friendly. Day list
    automatically filters to valid days for the selected month.
2026-05-10 feat(web): schedule zone editor improvements
    - Zone select auto-sizes to content width (no fixed w-40)
    - Duration label: 'Duration: 10m' inline, value larger (text-base bold)
    - + Add Zone collapses existing zones to summary, expands new one
    - Zone schedules sorted by zone number so same zone is grouped
    - Collapsed zone shows one-line summary; click to expand
    - New schedules start with first zone expanded, edit starts all collapsed
2026-05-10 fix(web): duration slider 1-min steps throughout, empty schedule message
    - Duration slider: 1-minute resolution for full range 1m–4h
    (was snapping to 15-min above 1h)
    - Empty schedules: explains that BLE-created schedules aren't
    automatically synced to the cloud backend yet
2026-05-10 fix(server): block M2M tokens from creating user records
    M2M client-credential tokens (sub ending in @clients) were being
    persisted as User rows, causing email unique constraint violations
    when real users logged in. Now returns 403 for machine tokens.
2026-05-10 feat(firmware): instant MQTT schedule sync on BLE mutations
    BleServer.onScheduleChanged callback fires immediately after any
    create/update/delete/activate/deactivate schedule command via BLE.
    Wired in main.cpp to mqttManager.publishSchedules() so the web
    dashboard reflects BLE changes within seconds, not up to 60s.
2026-05-10 fix(web): skip Auth0 consent screen on login
    Add prompt: 'login' to force login screen without consent dialog
2026-05-10 feat(server): MQTT connection health grading with tests
    - connectionMonitor.ts tracks per-device status pings in a 5-min rolling window
    - Grades each controller as good/degraded/poor/offline based on last-seen age and missed pings
    - good: last msg <30s, 0 missed pings
    - degraded: last msg 30-60s or 1-2 missed pings
    - poor: last msg 60-120s or 3+ missed pings (recommendLocalMode: true)
    - offline: last msg >120s (recommendLocalMode: true)
2026-05-10 feat(auth): add Create Account / registration flow
    Web:
    - Login page now shows 'Create Account' button alongside 'Sign In'
    - Login route passes screen_hint=signup to Auth0 when present
    Mobile:
    - Login screen now shows 'Create Account' button alongside 'Sign In'
    - auth.ts: added register() function that passes screen_hint: signup
2026-05-11 feat(firmware): log on/off toggle, suppress MQTT reconnect noise
    - Logger: add setVerbose(bool)/isVerbose() — log() is a no-op when muted
    - CLI: 'log off' mutes all background output, 'log on' restores; numeric
    'log [N]' behavior unchanged; help updated
    - MqttManager: suppress repeated connect-fail noise — prints on attempt 1
    then once per minute (every 6 × 10s); resets on begin() so a new broker
    config always gets a fresh first-attempt message
2026-05-11 fix(mobile): remove gray corner artifact on zone badges by keeping borderWidth constant
2026-05-11 feat(firmware): add RSSI and SNR quality ratings to wifi-status CLI and API
2026-05-11 fix(mobile): skip BLE load() in Settings when in cloud mode, add .env with LAN backend URL
